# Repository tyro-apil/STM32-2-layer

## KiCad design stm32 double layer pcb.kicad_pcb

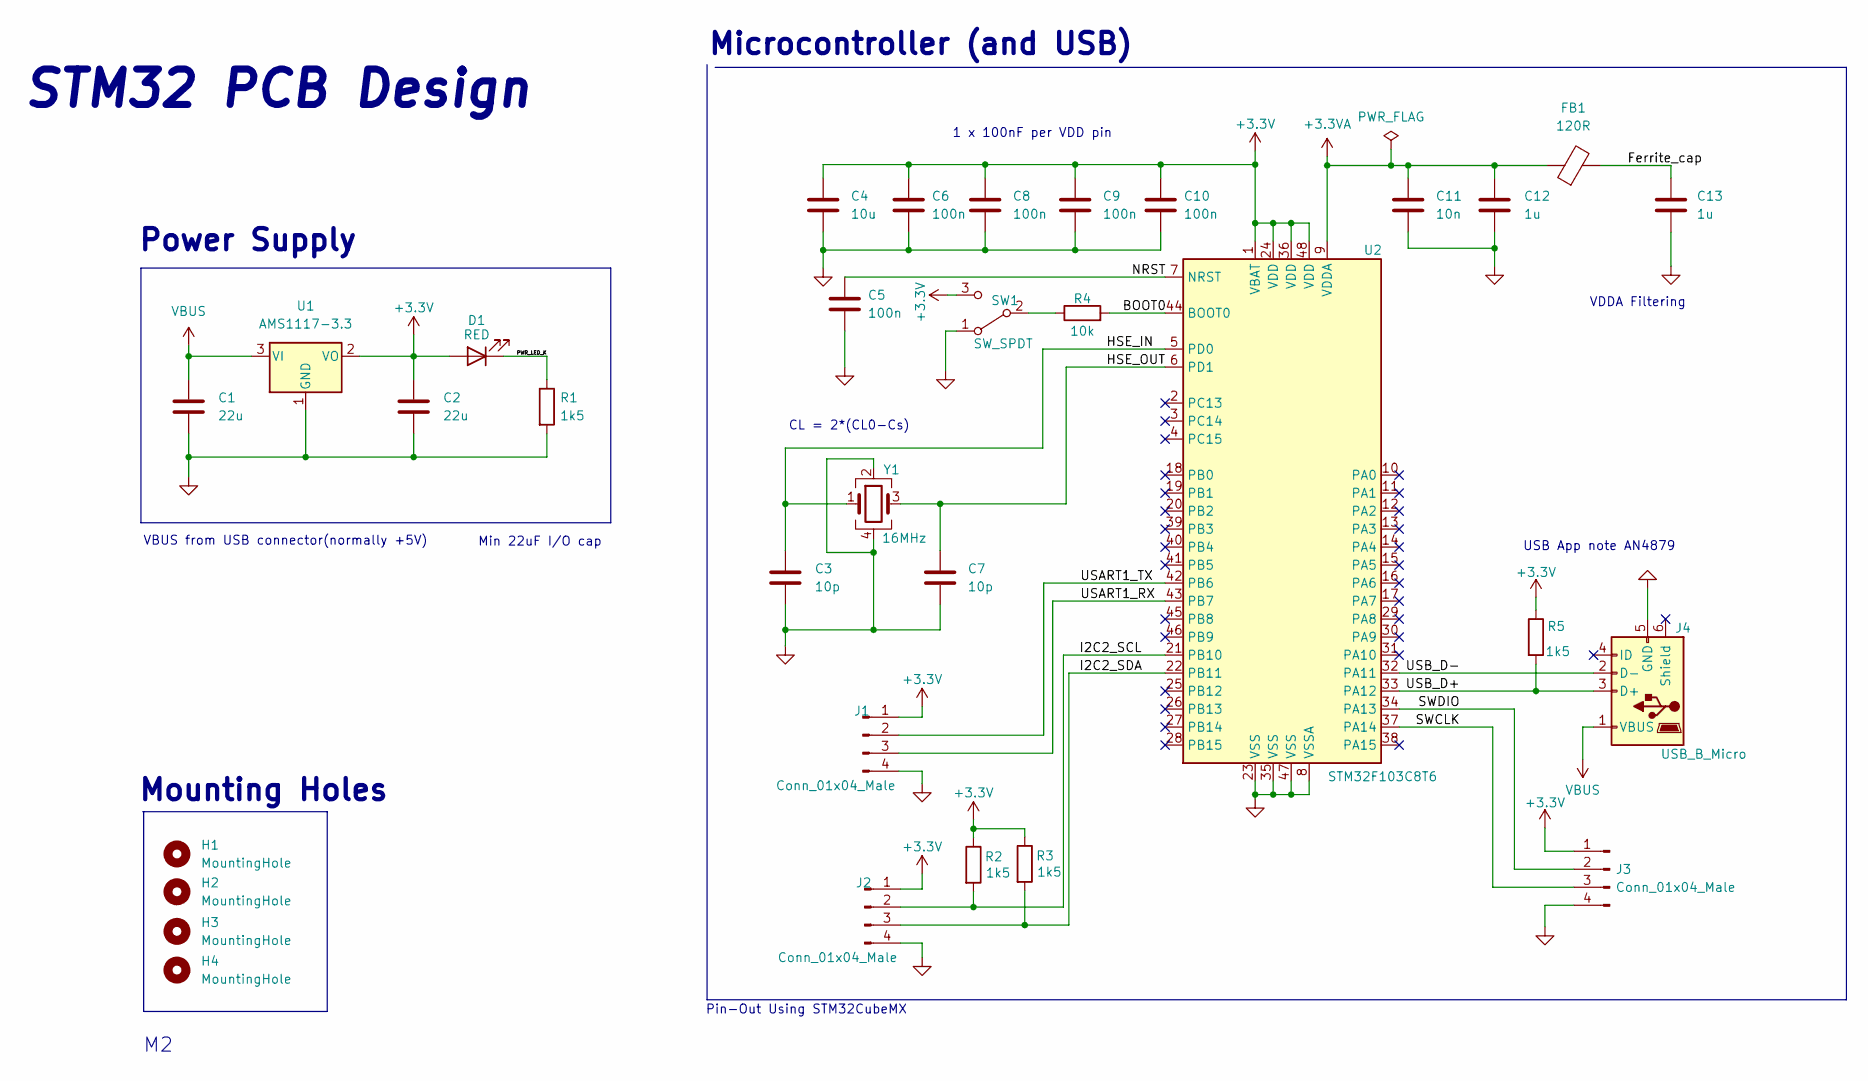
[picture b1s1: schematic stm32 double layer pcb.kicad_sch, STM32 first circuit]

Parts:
C1, C2: 22u; C_0805_2012Metric
C3, C7: 10p; C_0402_1005Metric
C4: 10u; C_0603_1608Metric
C5, C6, C8, C9, C10: 100n; C_0402_1005Metric
C11: 10n; C_0402_1005Metric
C12, C13: 1u; C_0402_1005Metric
D1: RED; LED_0201_0603Metric
FB1: 120R; L_0201_0603Metric
H1, H2, H3, H4: MountingHole; MountingHole_2.2mm_M2
J1, J2, J3: Conn_01x04_Male; PinHeader_1x04_P2.54mm_Vertical
J4: USB_B_Micro; USB_Micro-B_Wuerth_629105150521
R1, R2, R3, R5: 1k5; R_0402_1005Metric
R4: 10k; R_0402_1005Metric
SW1: SW_SPDT; SW_SPDT_PCM12
U1: AMS1117-3.3; SOT-223-3_TabPin2
U2: STM32F103C8T6; LQFP-48_7x7mm_P0.5mm
Y1: 16MHz; Crystal_SMD_3225-4Pin_3.2x2.5mm

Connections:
+3.3V: C2.1, C4.1, C6.1, C8.1, C9.1, C10.1, D1.2 (A), J1.1, J2.1, J3.1, R2.1, R3.1, R5.1, SW1.3 (C), U1.2 (VO), U2.1 (VBAT), U2.24 (VDD), U2.36 (VDD), U2.48 (VDD)
+3.3VA: C11.1, C12.1, FB1.1, U2.9 (VDDA)
/BOOT0: R4.2, U2.44 (BOOT0)
/Ferrite_cap: C13.1, FB1.2
/HSE_IN: C3.1, U2.5 (PD0), Y1.1
/HSE_OUT: C7.1, U2.6 (PD1), Y1.3
/I2C2_SCL: J2.2, R2.2, U2.21 (PB10)
/I2C2_SDA: J2.3, R3.2, U2.22 (PB11)
/NRST: C5.1, U2.7 (NRST)
/PWR_LED_K: D1.1 (K), R1.1
/SWCLK: J3.3, U2.37 (PA14)
/SWDIO: J3.2, U2.34 (PA13)
/USART1_RX: J1.3, U2.43 (PB7)
/USART1_TX: J1.2, U2.42 (PB6)
/USB_D+: J4.3 (D+), R5.2, U2.33 (PA12)
/USB_D-: J4.2 (D-), U2.32 (PA11)
GND: C1.2, C2.2, C3.2, C4.2, C5.2, C6.2, C7.2, C8.2, C9.2, C10.2, C11.2, C12.2, C13.2, J1.4, J2.4, J3.4, J4.5 (GND), R1.2, SW1.1 (A), U1.1 (GND), U2.8 (VSSA), U2.23 (VSS), U2.35 (VSS), U2.47 (VSS), Y1.2, Y1.4
unnamed: R4.1, SW1.2 (B)
VBUS: C1.1, J4.1 (VBUS), U1.3 (VI)

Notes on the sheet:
STM32 PCB Design
Mounting Holes
VBUS from USB connector(normally +5V)
1 x 100nF per VDD pin
Pin-Out Using STM32CubeMX
Power Supply
USB App note AN4879
VDDA Filtering
Microcontroller (and USB)
Min 22uF I/O cap
CL = 2*(CL0-Cs)

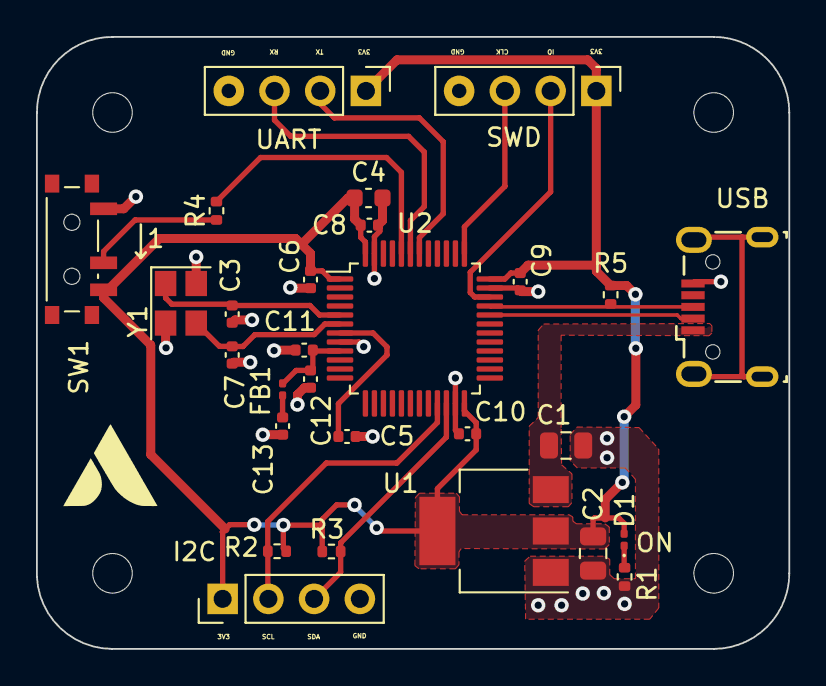
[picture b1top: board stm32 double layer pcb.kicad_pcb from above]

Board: 2 copper layers, 41.8 x 34.0 mm, 32 parts (0 on the bottom side), 19 nets.

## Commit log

2023-05-01 STM32 dual layer pcb with external voltage regulator, external crystal oscillator
